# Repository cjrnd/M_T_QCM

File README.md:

## Hardware for QCMD 
This repo contains all hardware needed for master thesis QCM project. CAD files for the EMI contraption. KiCad files for the PCBs both for the QCM driver and the power amplifier.

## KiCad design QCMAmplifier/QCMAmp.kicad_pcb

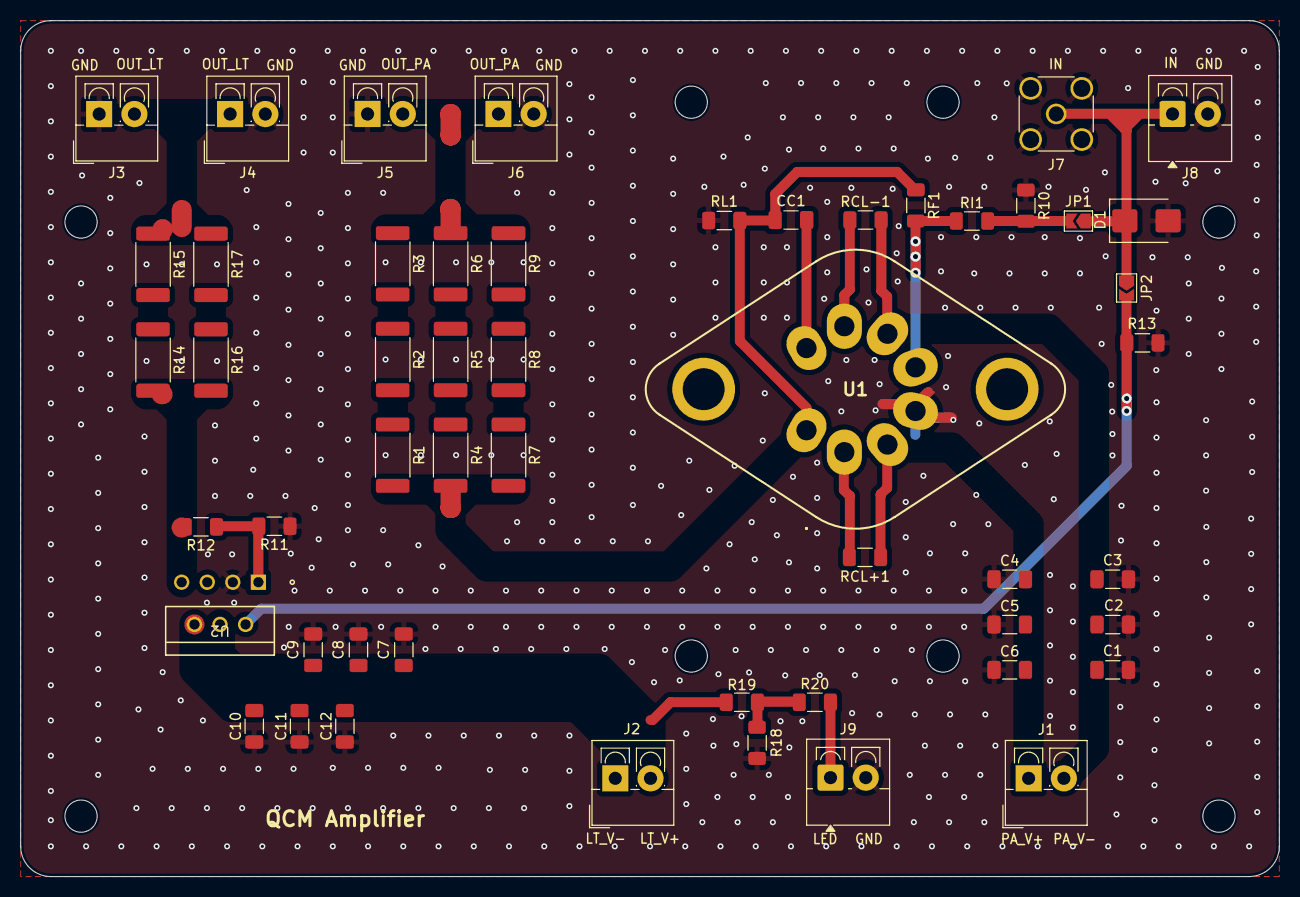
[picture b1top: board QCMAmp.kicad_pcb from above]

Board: 2 copper layers, 125.0 x 85.0 mm, 60 parts (0 on the bottom side), 27 nets.

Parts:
C1, C6, C9, C12: 10uF; C_1206_3216Metric_Pad1.33x1.80mm_HandSolder
C2, C5, C8, C11: 100nF; C_1206_3216Metric_Pad1.33x1.80mm_HandSolder
C3, C4, C7, C10: 1nF; C_1206_3216Metric_Pad1.33x1.80mm_HandSolder
CC1: C; C_1206_3216Metric_Pad1.33x1.80mm_HandSolder
D1: TVS 10-12V; D_SMB
H1, H2, H3, H4, H5, H6, H7, H8: MountingHole; MountingHole_3.2mm_M3
J1, J2, J3, J4, J5, J6, J8, J9: Screw_Terminal_01x02; TerminalBlock_4Ucon_1x02_P3.50mm_Vertical
J7: Screw_Terminal_01x02; SMA_Amphenol_132134_Vertical
JP1, JP2: Jumper_2_Bridged; SolderJumper-2_P1.3mm_Open_TrianglePad1.0x1.5mm
R1, R2, R3, R4, R5, R6, R7, R8, R9, R14, R15, R16, R17: 50; R_2512_6332Metric_Pad1.40x3.35mm_HandSolder
R10, R13: DNP; R_1206_3216Metric_Pad1.30x1.75mm_HandSolder
R11: 220; R_1206_3216Metric_Pad1.30x1.75mm_HandSolder
R12: 680; R_1206_3216Metric_Pad1.30x1.75mm_HandSolder
R18, R19, R20: 1000; R_1206_3216Metric_Pad1.30x1.75mm_HandSolder
RCL+1: R; R_1206_3216Metric_Pad1.30x1.75mm_HandSolder
RCL-1: R; R_1206_3216Metric_Pad1.30x1.75mm_HandSolder
RF1: R; R_1206_3216Metric_Pad1.30x1.75mm_HandSolder
RI1: R; R_1206_3216Metric_Pad1.30x1.75mm_HandSolder
RL1: R; R_1206_3216Metric_Pad1.30x1.75mm_HandSolder
U1: PA119CE; PA08
U2: LT1210CT7-PBF; TO220-7_T_LIT

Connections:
+15V: C7.2, C8.2, C9.2, J2.2, R19.2, U2.4 (V+)
+36V: C4.2, C5.2, C6.2, J1.1, RCL+1.2, U1.3 (+VS)
-15V: C10.2, C11.2, C12.2, J2.1, U2.6 (V-)
-36V: C1.2, C2.2, C3.2, J1.2, RCL-1.2, U1.6 (-VS)
/IN: D1.1 (A1), J7.1, J8.1, JP1.1 (A), JP2.1 (A)
/OUT_LT: J3.2, J4.1, R15.1, R17.1
/OUT_LT_R: R12.2, R14.2, R16.2, U2.7 (OUT)
/OUT_PA: J5.2, J6.1, R3.1, R6.1, R9.1
/OUT_PA_R: CC1.1, R1.2, R4.2, R7.2, RF1.1, RL1.1, U1.1 (OUT)
GND: C1.1, C2.1, C3.1, C4.1, C5.1, C6.1, C7.1, C8.1, C9.1, C10.1, C11.1, C12.1, D1.2 (A2), J3.1, J4.2, J5.1, J6.2, J7.2, J8.2, J9.2, R10.1, R11.1, R13.1, R18.1, RL1.2, U1.4 (+IN), U2.3 (SD)
unnamed: J9.1, R20.2
unnamed: JP1.2 (B), R10.2, RI1.2
unnamed: JP2.2 (B), R13.2, U2.2 (IN+)
unnamed: R1.1, R2.2
unnamed: R2.1, R3.2
unnamed: R4.1, R5.2
unnamed: R5.1, R6.2
unnamed: R7.1, R8.2
unnamed: R8.1, R9.2
unnamed: R14.1, R15.2
unnamed: R16.1, R17.2
unnamed: R18.2, R19.1, R20.1
unnamed: RCL+1.1, U1.2 (+CL)
unnamed: RCL-1.1, U1.7 (-CL)
unnamed: RF1.2, RI1.1, U1.5 (-IN)
unnamed: CC1.2, U1.8 (CC)
unnamed: R11.2, R12.1, U2.1 (IN-)

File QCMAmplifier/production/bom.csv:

Designator,Footprint,Quantity,Value,LCSC Part #
"C1, C12, C6, C9",1206,4,10uF,
"C10, C3, C4, C7",1206,4,1nF,
"C11, C2, C5, C8",1206,4,100nF,
CC1,1206,1,C,
D1,D_SMB,1,TVS 10-12V,
"J1, J2, J3, J4, J5, J6, J8, J9",TerminalBlock_4Ucon_1x02_P3.50mm_Vertical,8,Screw_Terminal_01x02,
J7,SMA_Amphenol_132134_Vertical,1,Screw_Terminal_01x02,
"JP1, JP2",SolderJumper-2_P1.3mm_Open_TrianglePad1.0x1.5mm,2,Jumper_2_Bridged,
"R1, R14, R15, R16, R17, R2, R3, R4, R5, R6, R7, R8, R9",2512,13,50,
"R10, R13",1206,2,DNP,
R11,1206,1,220,
R12,1206,1,680,
"R18, R19, R20",1206,3,1000,
"RCL+1, RCL-1, RF1, RI1, RL1",1206,5,R,
U1,PA08,1,PA119CE,
U2,TO220-7_T_LIT,1,LT1210CT7-PBF,

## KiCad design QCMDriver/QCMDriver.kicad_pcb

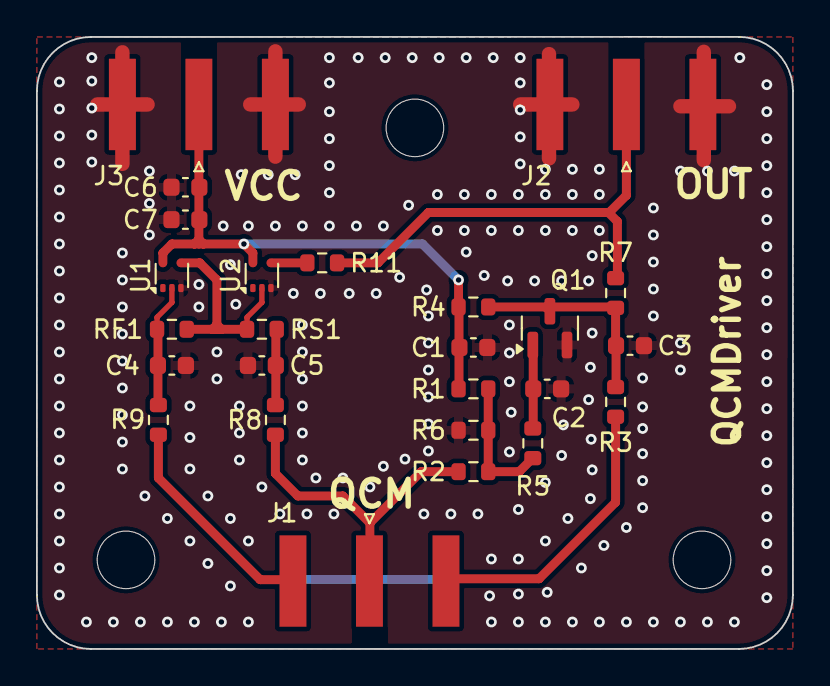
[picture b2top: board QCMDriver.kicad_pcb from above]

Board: 2 copper layers, 42.0 x 34.0 mm, 28 parts (0 on the bottom side), 12 nets.

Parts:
C1, C7: 100nF; C_0603_1608Metric
C2: 100pF; C_0603_1608Metric
C3: 27pF; C_0603_1608Metric
C4, C5: 32pF; C_0603_1608Metric
C6: 10uF; C_0603_1608Metric
H1, H2, H3: MountingHole; MountingHole_3.2mm_M3
J1, J2, J3: Conn_Coaxial; SMA_Amphenol_132289_EdgeMount
Q1: BC817; SOT-23
R1: 4.7k; R_0603_1608Metric
R2, R3, R7, R8, R9, R11: 0; R_0603_1608Metric
R4: 1k; R_0603_1608Metric
R5: 47k; R_0603_1608Metric
R6: 1.5k; R_0603_1608Metric
RF1: 2.2M; R_0603_1608Metric
RS1: 1k; R_0603_1608Metric
U1, U2: 74LVC1GU04DRL; SOT-553

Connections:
/OUT_OSC: J2.1 (In), R7.2, R11.2
/QCMA: J1.1 (In), R2.1, R8.1
/QCMB: J1.2 (Ext), R3.1, R9.1
GND: C1.2, C2.2, C3.2, C4.2, C5.2, C6.2, C7.2, J2.2 (Ext), J3.2 (Ext), Q1.2 (E), R6.2, U1.3 (GND), U2.3 (GND)
unnamed: C4.1, R9.2, RF1.1, U1.2
unnamed: C5.1, R8.2, RS1.2
unnamed: C2.1, Q1.1 (B), R5.2
unnamed: C3.1, Q1.3 (C), R3.2, R4.2, R7.1
unnamed: R1.2, R2.2, R5.1, R6.1
unnamed: R11.1, U2.4
unnamed: RF1.2, RS1.1, U1.4, U2.2
VCCOSC: C1.1, C6.1, C7.1, J3.1 (In), R1.1, R4.1, U1.5 (VCC), U2.5 (VCC)

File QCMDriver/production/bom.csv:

Designator,Footprint,Quantity,Value,LCSC Part #
"C1, C7",0603,2,100nF,
C2,0603,1,100pF,
C3,0603,1,27pF,
"C4, C5",0603,2,32pF,
C6,0603,1,10uF,
"J1, J2, J3",SMA_Amphenol_132289_EdgeMount,3,Conn_Coaxial,
Q1,SOT-23,1,BC817,
R1,0603,1,4.7k,
"R11, R2, R3, R7, R8, R9",0603,6,0,
"R4, RS1",0603,2,1k,
R5,0603,1,47k,
R6,0603,1,1.5k,
RF1,0603,1,2.2M,
"U1, U2",SOT-553,2,74LVC1GU04DRL,

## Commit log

2025-03-15 init commit
2025-03-16 amplifier board added
2025-03-16 cad files
2025-03-18 vcc caps and vias added, minor layout improvements
2025-03-18 changes in schematic
2025-03-21 misc improvements
2025-03-21 changes made, gerbers added
2025-03-24 changes in dimensions
2025-03-24 stp files added
2025-03-26 cleanup
2025-05-08 script for auto data read from dmm
2025-05-11 csv file generation fixed
2025-05-12 simple gui added
2025-06-04 Rename visa_read_data.py to visa_read_data1.py
2025-06-04 new version
2025-06-05 windows working code
